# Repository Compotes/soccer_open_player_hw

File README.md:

# soccer_open_player_hw
Schematics and board designs for PCBs for our Robocup junior Open Soccer player robot.
All PCBs are designed in EagleCAD. <br>
Here you can find software we developed for our boards: <br>
[Driver](https://github.com/Compotes/driver_board) <br>
[Kicker](https://github.com/Compotes/kicker_board) <br>
[Lines](https://github.com/Compotes/lines_board) <br>
[Master](https://github.com/Compotes/master_board) <br>

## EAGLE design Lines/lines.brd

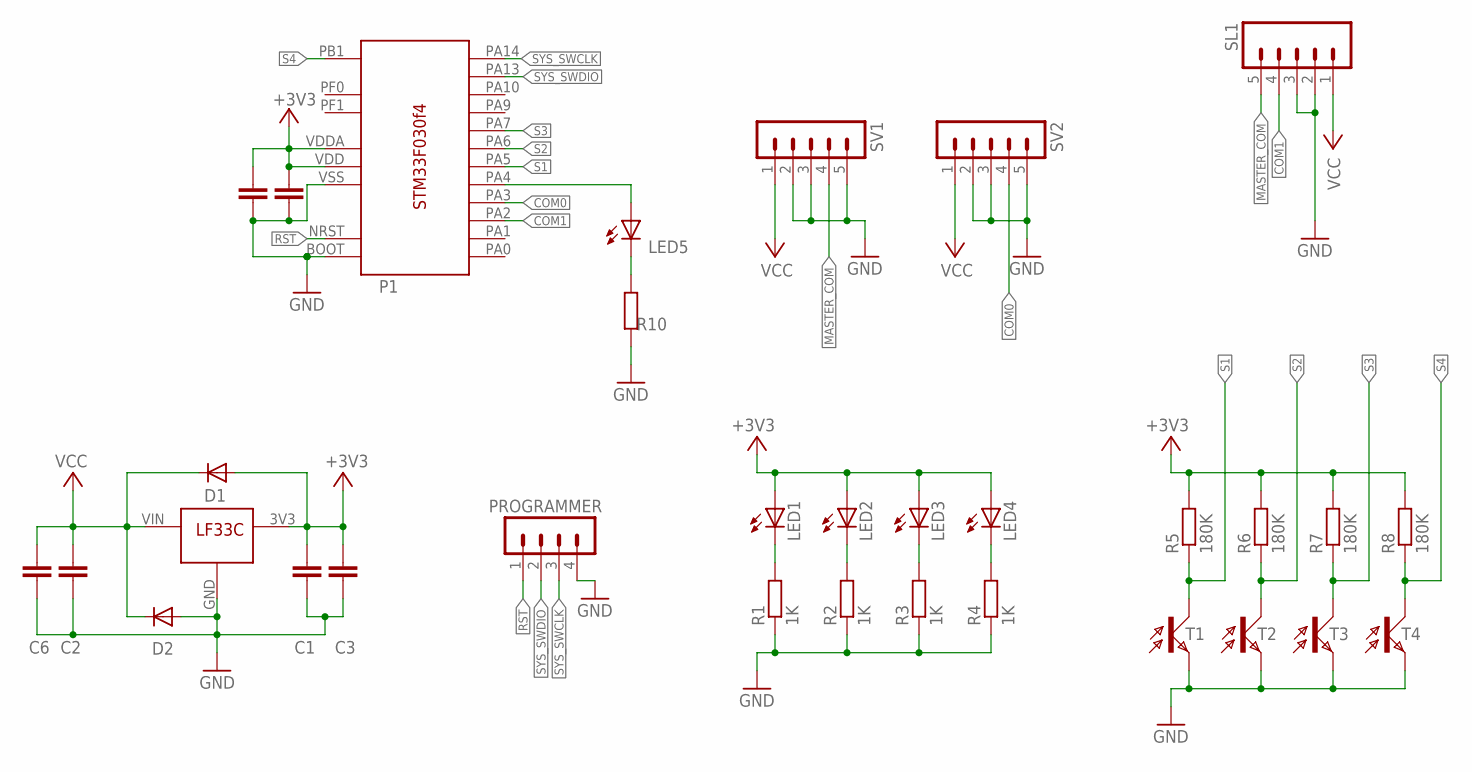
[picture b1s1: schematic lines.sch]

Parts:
C1, C2: 100k; C0603
C3, C6: 10u; C1206
C4, C5: 100K; C0603
D1, D2: DIODE-MINIMELF; MINIMELF
LED1, LED2, LED3, LED4: LED5MM
LED5: LED_E; LED_1206
P1: STM32F030F4
PROGRAMMER: MA04-1
R1, R2, R3, R4: 1K; R0603
R5, R6, R7, R8: 180K; R0603
R10: R-EU_R0603; R0603
SL1: M05; 05P
SV1, SV2: MA05-1
T1, T2, T3, T4: BPX81
U$1: LF33C

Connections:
+3V3: C1.1, C3.1, C4.1, C5.1, D1.A, LED1.A, LED2.A, LED3.A, LED4.A, P1.VDD, P1.VDDA, R5.2, R6.2, R7.2, R8.2, U$1.3V3
COM0: P1.PA3, SV2.4
FROM_MASTER: SL1.5, SV1.4
GND: C1.2, C2.2, C3.2, C4.2, C5.2, C6.2, D2.A, P1.BOOT, P1.VSS, PROGRAMMER.4, R1.1, R2.1, R3.1, R4.1, R10.1, SL1.2, SL1.3, SV1.2, SV1.3, SV1.5, SV2.2, SV2.3, SV2.5, T1.E, T2.E, T3.E, T4.E, U$1.GND
unnamed: LED1.K (C), R1.2
unnamed: LED2.K (C), R2.2
unnamed: LED3.K (C), R3.2
unnamed: LED4.K (C), R4.2
unnamed: LED5.C, R10.2
unnamed: LED5.A, P1.PA4
RST: P1.NRST, PROGRAMMER.1
S1: P1.PA5, R5.1, T1.C
S2: P1.PA6, R6.1, T2.C
S3: P1.PA7, R7.1, T3.C
S4: P1.PB1, R8.1, T4.C
SYS_SWCLK: P1.PA14, PROGRAMMER.3
SYS_SWDIO: P1.PA13, PROGRAMMER.2
TO_MASTER: P1.PA2, SL1.4
VCC: C2.1, C6.1, D1.C, D2.C, SL1.1, SV1.1, SV2.1, U$1.VIN

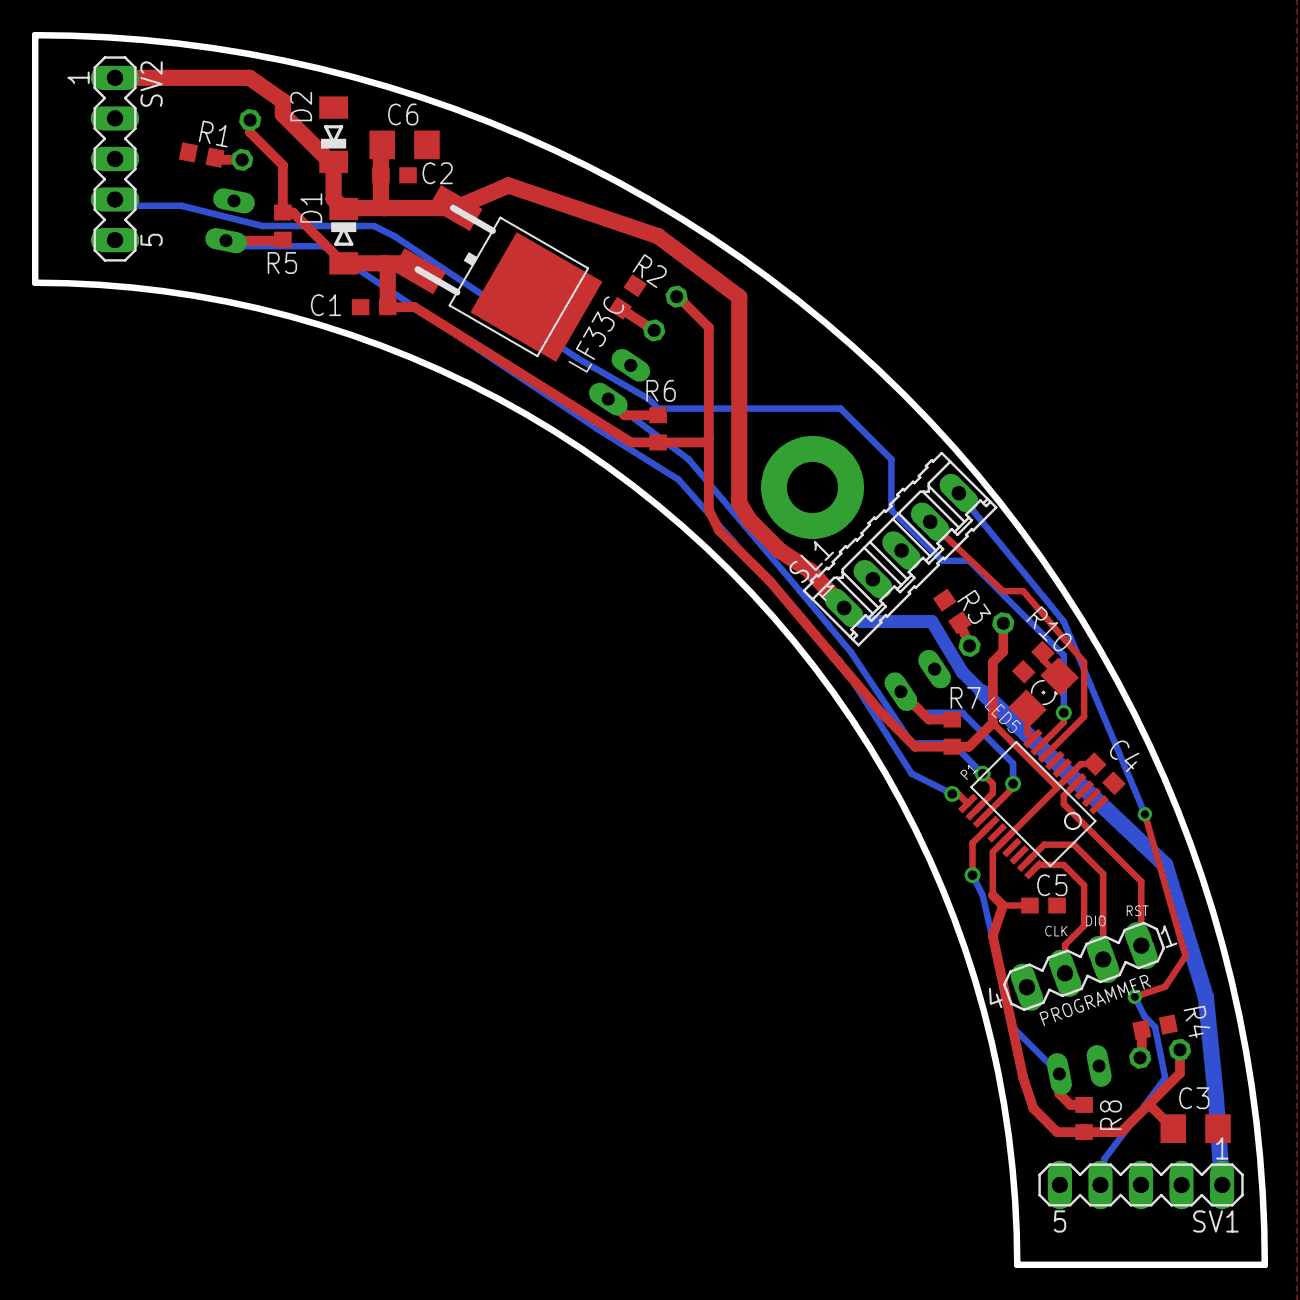
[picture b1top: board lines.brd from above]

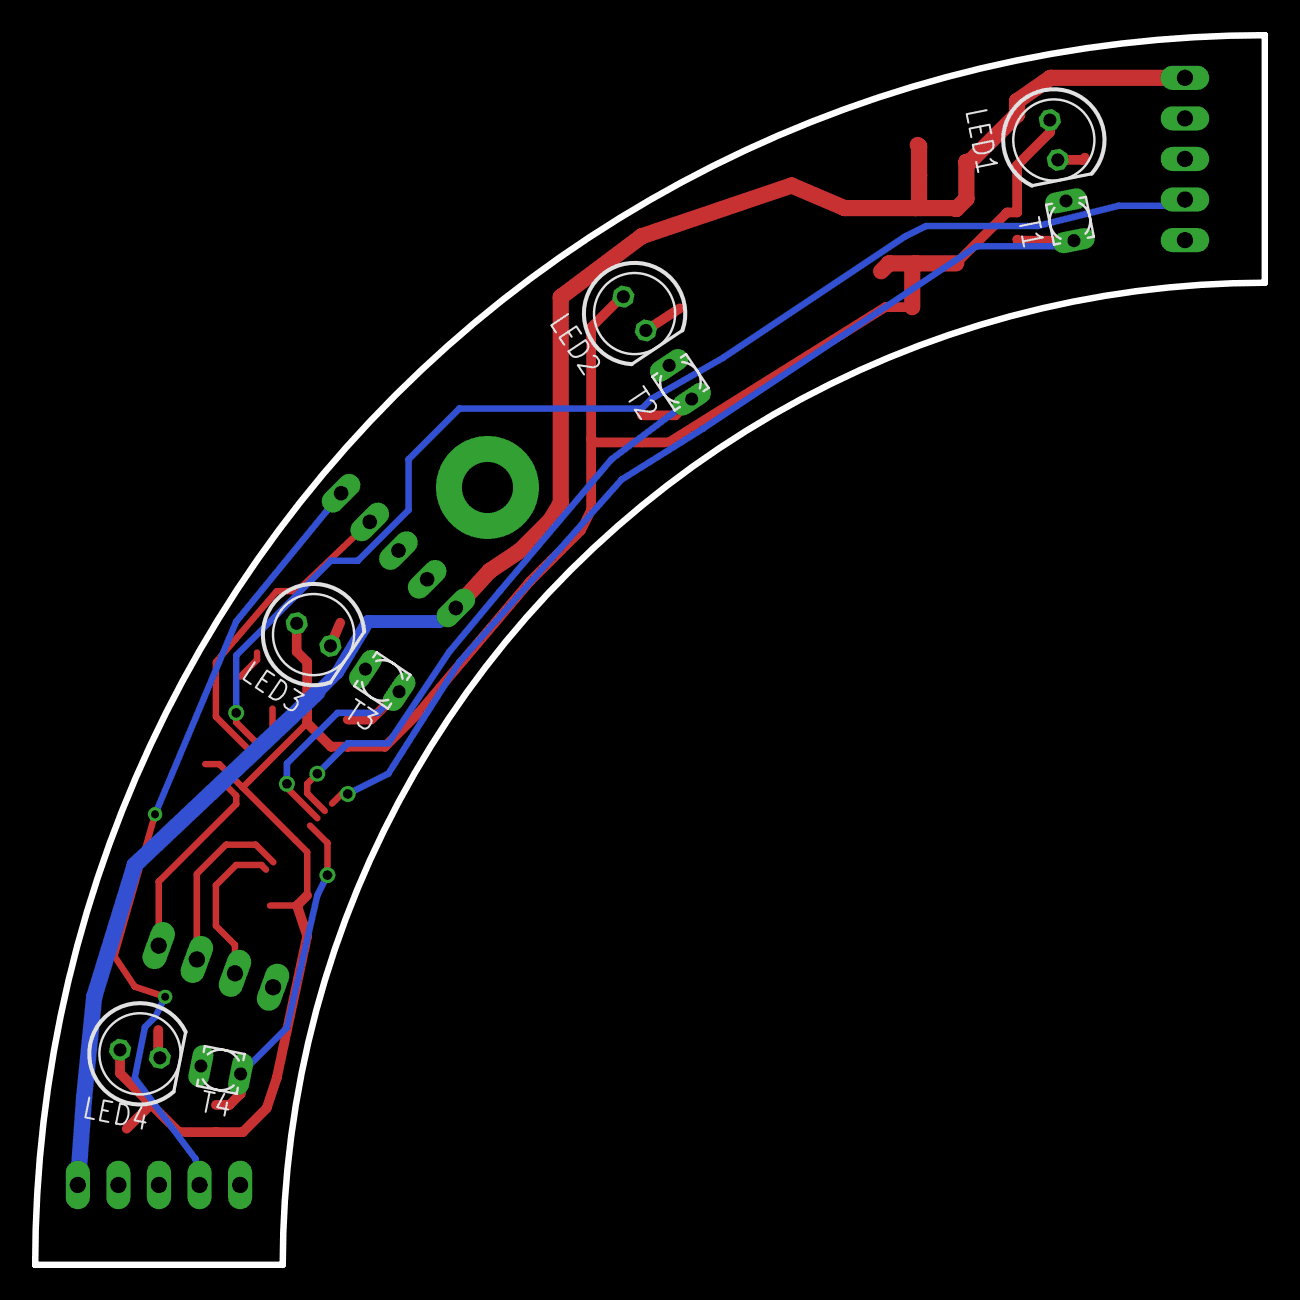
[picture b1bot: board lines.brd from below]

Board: 2 copper layers, 77.0 x 77.0 mm, 32 parts (8 on the bottom side), 19 nets.

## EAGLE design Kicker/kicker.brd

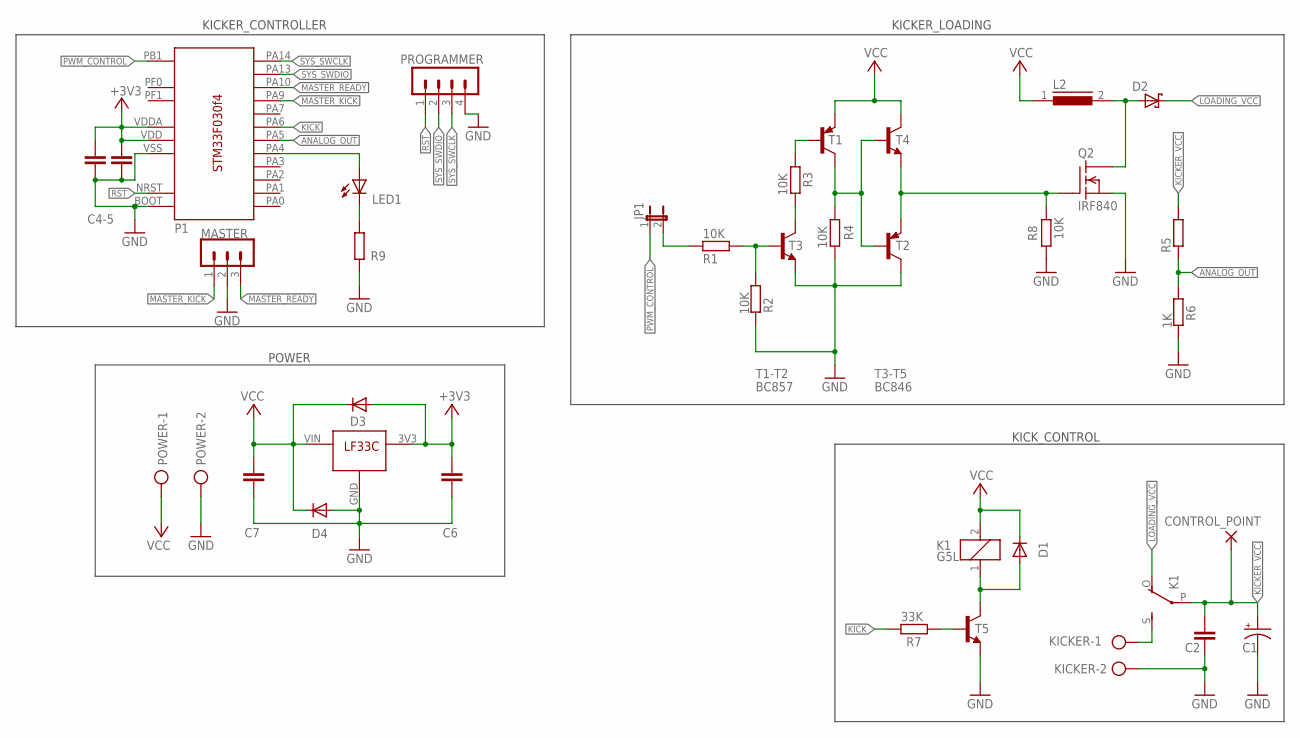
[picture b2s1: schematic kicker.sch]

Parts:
C1: CPOL-USE10-30; EB30D
C2: C-EU275-113X316; C275-113X316
C4, C5: 100K; C0603
C6, C7: 100k; C0603
CONTROL_POINT: 3,81/1,4
D1, D3, D4: DIODE-MINIMELF; MINIMELF
D2: 1N6267A; C4111-15
JP1: JP1E; JP1
K1: G5L; G5LE
KICKER: W237-102
L2: SFT830S
LED1: LED_E; LED_1206
MASTER: MA03-1
P1: STM32F030F4
POWER: W237-102
PROGRAMMER: MA04-1
Q2: IRF840; TO220
R1, R2, R3, R4, R8: 10K; R0603
R5: R-EU_0309/10; 0309/10
R6: 1K; R0603
R7: 33K; R0603
R9: R-EU_R0603; R0603
T1, T2: BC856A-PNP-SOT23-BEC; SOT23-BEC
T3, T4, T5: BC847; SOT23
U$1: LF33C

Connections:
+3V3: C4.1, C5.1, C6.1, D3.A, P1.VDD, P1.VDDA, U$1.3V3
ANALOG_OUT: P1.PA5, R5.1, R6.1
GND: C1.-, C2.2, C4.2, C5.2, C6.2, C7.2, D4.A, KICKER.2, MASTER.2, P1.BOOT, P1.VSS, POWER.2, PROGRAMMER.4, Q2.3 (S), R2.2, R4.2, R6.2, R8.1, R9.1, T2.C, T3.2 (E), T5.2 (E), U$1.GND
KICK: P1.PA6, R7.2
KICKER_VCC: C1.+, C2.1, CONTROL_POINT.1, K1.P, R5.2
LOADING_VCC: D2.C, K1.O
MASTER_KICK: MASTER.1, P1.PA9
MASTER_READY: MASTER.3, P1.PA10
unnamed: R7.1, T5.1 (B)
unnamed: JP1.2, R1.2
unnamed: K1.S, KICKER.1
unnamed: D1.A, K1.1, T5.3 (C)
unnamed: R1.1, R2.1, T3.1 (B)
unnamed: LED1.C, R9.2
unnamed: LED1.A, P1.PA4
unnamed: R3.1, T1.B
unnamed: R3.2, T3.3 (C)
unnamed: R4.1, T1.C, T2.B, T4.1 (B)
unnamed: Q2.1 (G), R8.2, T2.E, T4.2 (E)
unnamed: D2.A, L2.2, Q2.2 (D)
PWM_CONTROL: JP1.1, P1.PB1
RST: P1.NRST, PROGRAMMER.1
SYS_SWCLK: P1.PA14, PROGRAMMER.3
SYS_SWDIO: P1.PA13, PROGRAMMER.2
VCC: C7.1, D1.C, D3.C, D4.C, K1.2, L2.1, POWER.1, T1.E, T4.3 (C), U$1.VIN

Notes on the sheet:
T1-T2
T3-T5
BC857
BC846
C4-5
KICK_CONTROL
KICKER_LOADING
KICKER_CONTROLLER
POWER

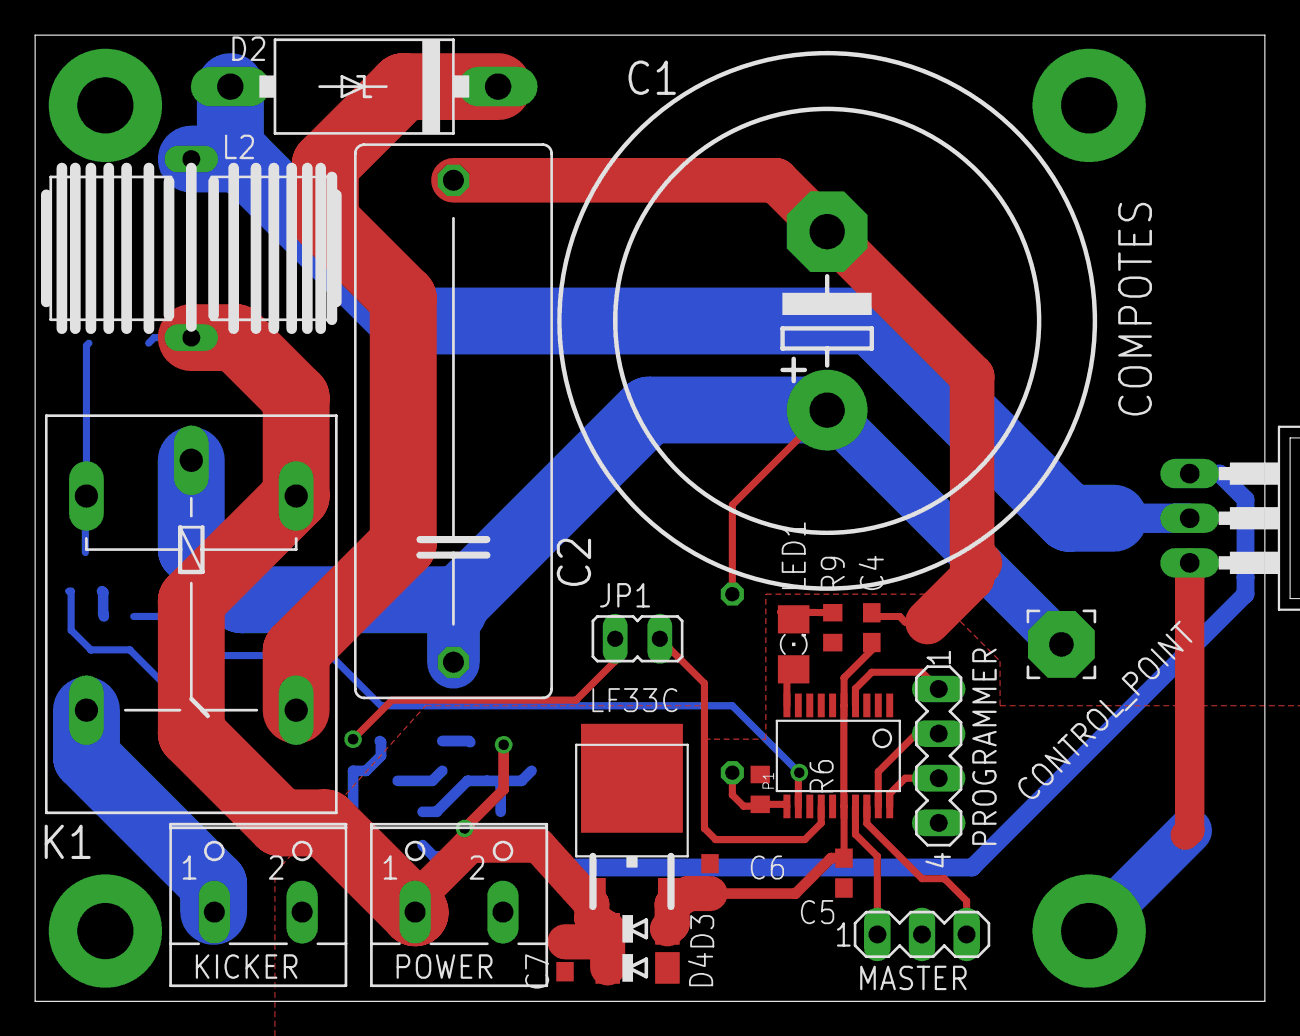
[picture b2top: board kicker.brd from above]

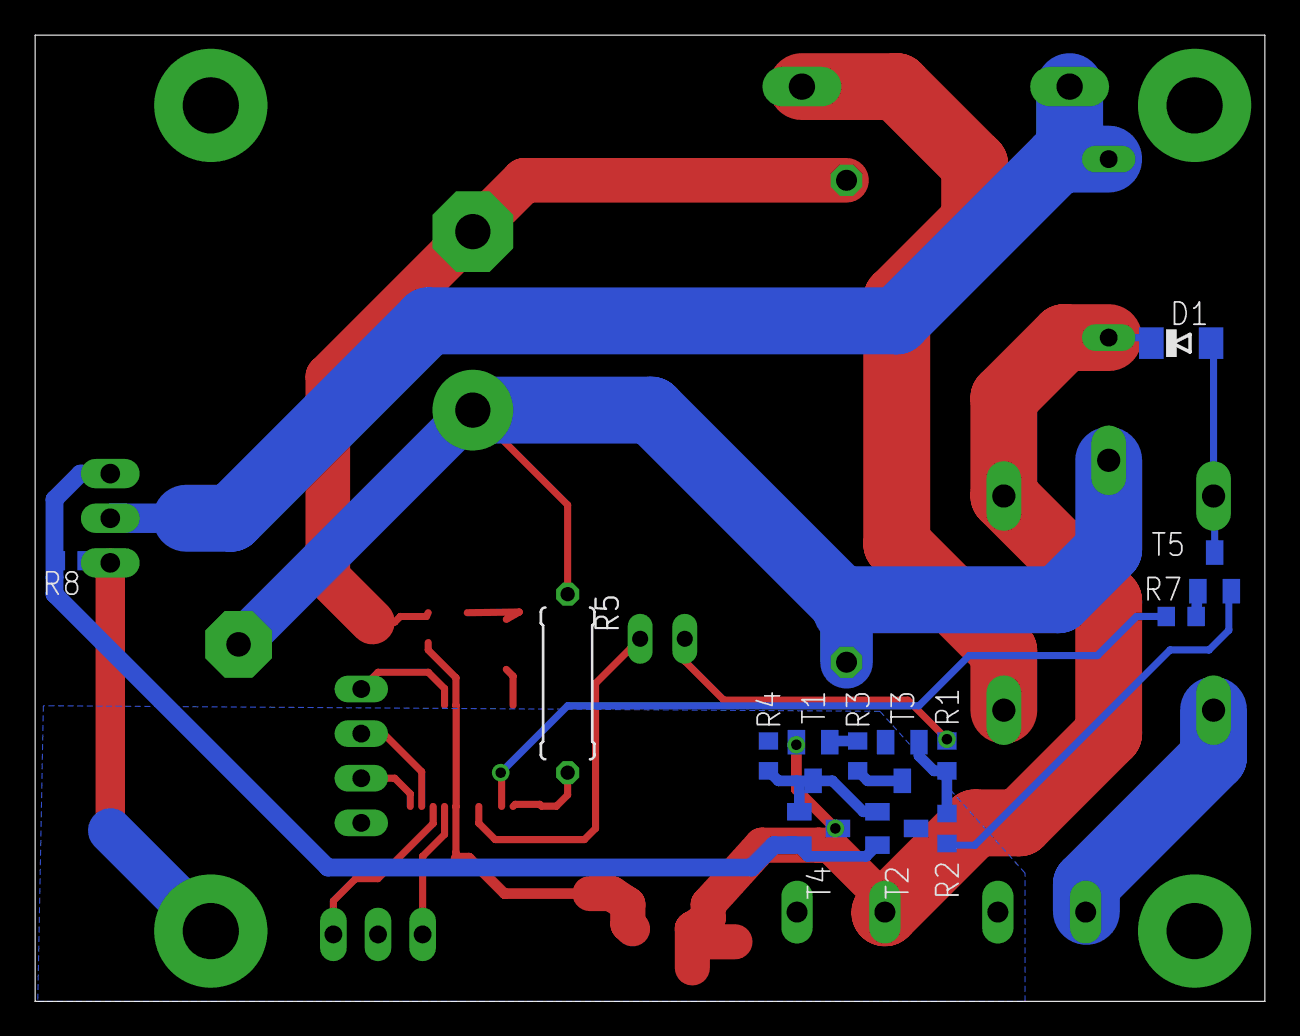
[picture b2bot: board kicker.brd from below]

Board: 2 copper layers, 70.0 x 55.0 mm, 36 parts (13 on the bottom side), 25 nets.

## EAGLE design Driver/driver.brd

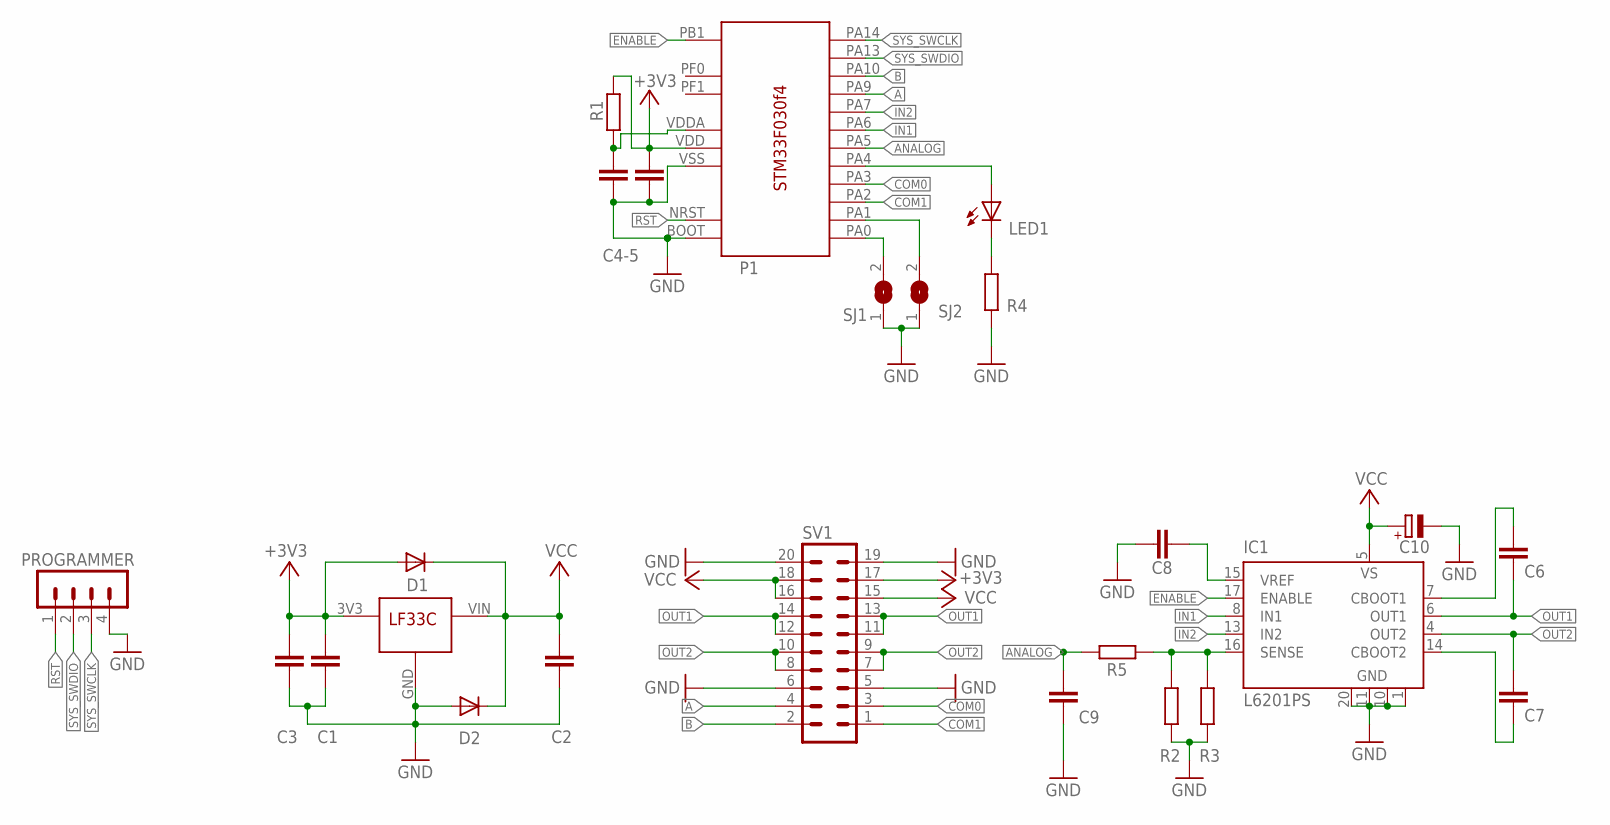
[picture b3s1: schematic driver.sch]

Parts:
C1, C2, C8, C9: 220k; C0603
C3: 10u; C1206
C4, C5: 100K; C0603
C6, C7: 15K; C0603
C10: CPOL-EUD/7343-31W; D/7343-31W
D1, D2: DIODE-MINIMELF; MINIMELF
IC1: L6201PS; POWERSO-20
LED1: LED_E; LED_1206
P1: STM32F030F4
PROGRAMMER: MA04-1
R1: R-EU_R1206; R1206
R2, R3: R1; R2512
R4, R5: R-EU_R0603; R0603
SJ1, SJ2: SJ
SV1: MA10-2W
U$1: LF33C

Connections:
+3V3: C1.1, C3.1, C5.1, D1.A, P1.VDD, R1.2, SV1.17, U$1.3V3
A: P1.PA9, SV1.4
ANALOG: C9.1, P1.PA5, R5.2
B: P1.PA10, SV1.2
COM0: P1.PA3, SV1.3
COM1: P1.PA2, SV1.1
ENABLE: IC1.17 (ENABLE), P1.PB1
GND: C1.2, C2.2, C3.2, C4.2, C5.2, C8.2, C9.2, C10.-, D2.A, IC1.1 (GND), IC1.10 (GND), IC1.11 (GND), IC1.20 (GND), P1.BOOT, P1.VSS, PROGRAMMER.4, R2.1, R3.1, R4.1, SJ1.1, SJ2.1, SV1.5, SV1.6, SV1.19, SV1.20, U$1.GND
IN1: IC1.8 (IN1), P1.PA6
IN2: IC1.13 (IN2), P1.PA7
unnamed: C4.1, P1.VDDA, R1.1
unnamed: C6.1, IC1.7 (CBOOT1)
unnamed: LED1.C, R4.2
unnamed: P1.PA0, SJ1.2
unnamed: C7.2, IC1.14 (CBOOT2)
unnamed: C8.1, IC1.15 (VREF)
unnamed: P1.PA1, SJ2.2
unnamed: LED1.A, P1.PA4
unnamed: IC1.16 (SENSE), R2.2, R3.2, R5.1
OUT1: C6.2, IC1.6 (OUT1), SV1.11, SV1.12, SV1.13, SV1.14
OUT2: C7.1, IC1.4 (OUT2), SV1.7, SV1.8, SV1.9, SV1.10
RST: P1.NRST, PROGRAMMER.1
SYS_SWCLK: P1.PA14, PROGRAMMER.3
SYS_SWDIO: P1.PA13, PROGRAMMER.2
VCC: C2.1, C10.+, D1.C, D2.C, IC1.5 (VS), SV1.15, SV1.16, SV1.18, U$1.VIN

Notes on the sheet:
C4-5

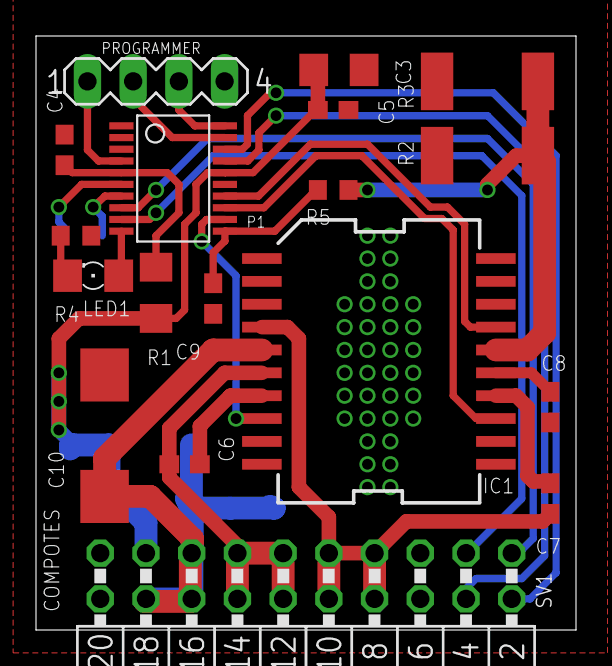
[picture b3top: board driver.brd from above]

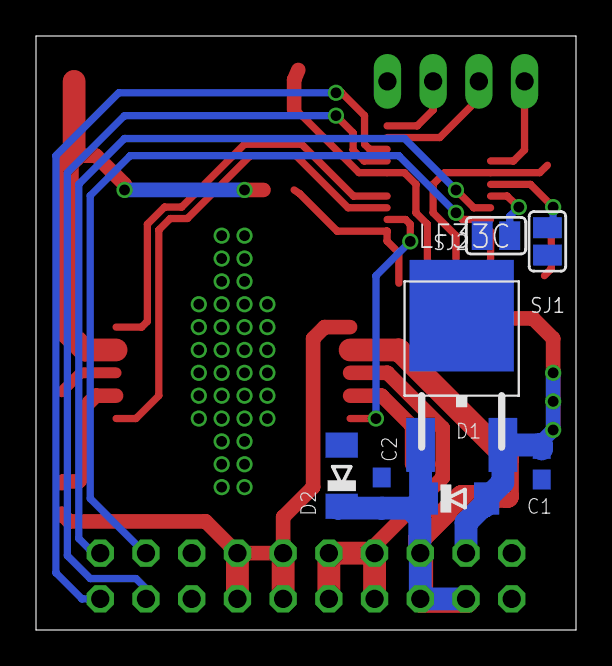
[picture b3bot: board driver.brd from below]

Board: 2 copper layers, 30.0 x 33.0 mm, 25 parts (7 on the bottom side), 25 nets.

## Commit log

2017-07-23 All files added.
